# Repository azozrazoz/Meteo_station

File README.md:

# METEO BRASLET V1

My first device on PCB

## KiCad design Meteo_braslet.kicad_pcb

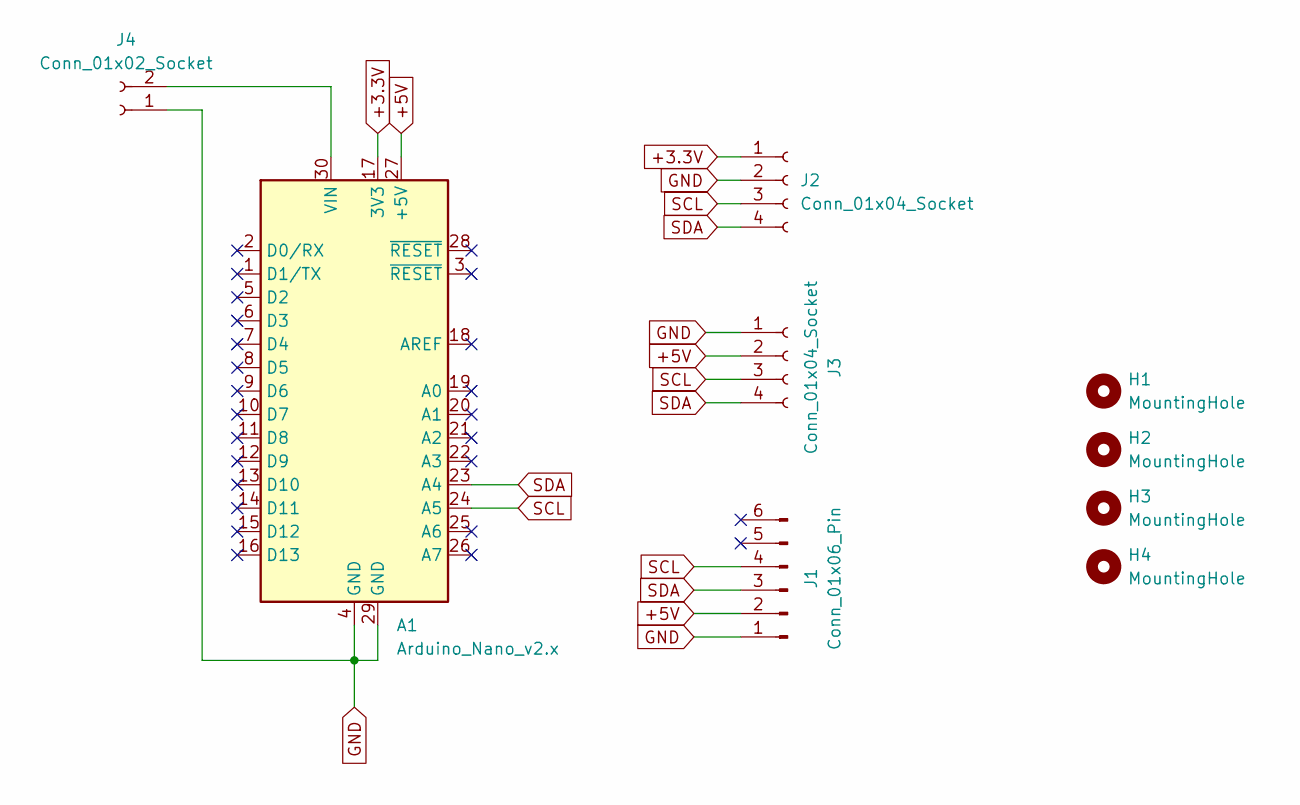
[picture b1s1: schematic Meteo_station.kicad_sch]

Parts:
A1: Arduino_Nano_v2.x; Arduino_Nano
H1, H2, H3, H4: MountingHole; MountingHole_2.5mm
J1: Conn_01x06_Pin; PinHeader_1x06_P2.54mm_Vertical
J2, J3: Conn_01x04_Socket; PinHeader_1x04_P2.54mm_Vertical
J4: Conn_01x02_Socket; PinHeader_1x02_P2.54mm_Vertical

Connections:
+3.3V: A1.17 (3V3), J2.1
+5V: A1.27 (+5V), J1.2, J3.2
GND: A1.4 (GND), A1.29 (GND), J1.1, J2.2, J3.1, J4.1
unnamed: A1.30 (VIN), J4.2
SCL: A1.24 (A5), J1.4, J2.3, J3.3
SDA: A1.23 (A4), J1.3, J2.4, J3.4

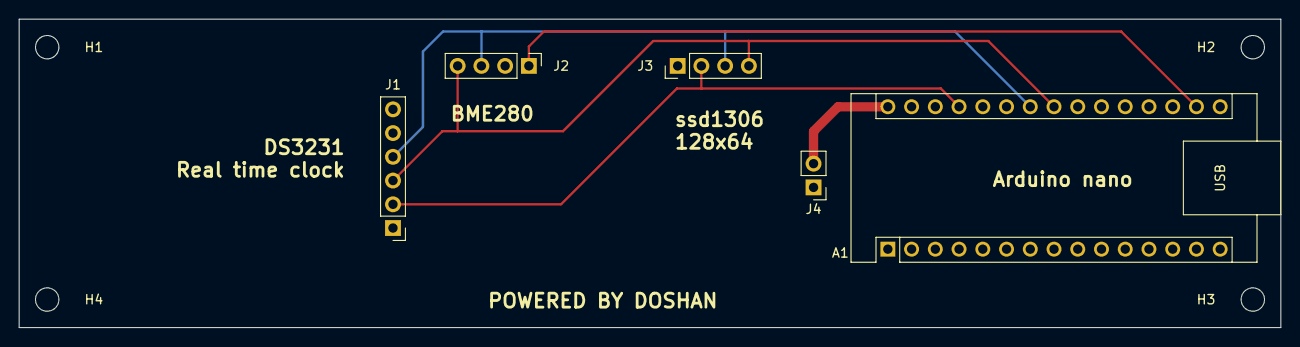
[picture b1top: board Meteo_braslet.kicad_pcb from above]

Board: 2 copper layers, 135.0 x 33.0 mm, 9 parts (0 on the bottom side), 6 nets.

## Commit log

2024-01-19 Rename Meteo_braslet.kicad_pcb to Meteo_staion.kicad_pcb
2024-01-19 Rename Meteo_braslet.kicad_prl to Meteo_staion.kicad_prl
2024-01-19 Rename Meteo_staion.kicad_prl to Meteo_station.kicad_prl
2024-01-19 Rename Meteo_staion.kicad_pcb to Meteo_station.kicad_pcb
2024-01-19 Rename Meteo_braslet.wrl to Meteo_station.wrl
2024-01-19 Rename Meteo_braslet.step to Meteo_station.step
2024-01-19 Rename Meteo_braslet.kicad_sch to Meteo_station.kicad_sch
2024-01-19 Rename Meteo_braslet.kicad_pro to Meteo_station.kicad_pro
2024-01-19 Rename Meteo_braslet-PTH.drl to Meteo_station-PTH.drl
2024-01-19 Rename Meteo_braslet-PTH-drl_map.gbr to Meteo_station-PTH-drl_map.gbr
2024-01-19 Rename Meteo_braslet-NPTH.drl to Meteo_station-NPTH.drl
2024-01-19 Rename Meteo_braslet-NPTH-drl_map.gbr to Meteo_station-NPTH-drl_map.gbr
2024-01-19 Rename Meteo_braslet-F_Silkscreen.gto to Meteo_station-F_Silkscreen.gto
2024-01-19 Rename Meteo_braslet-F_Paste.gtp to Meteo_station-F_Paste.gtp
2024-01-19 Rename Meteo_braslet-F_Mask.gts to Meteo_station-F_Mask.gts
2024-01-19 Rename Meteo_braslet-F_Cu.gtl to Meteo_station-F_Cu.gtl
2024-01-19 Rename Meteo_braslet-Edge_Cuts.gm1 to Meteo_station-Edge_Cuts.gm1
2024-01-19 Rename Meteo_braslet-B_Silkscreen.gbo to Meteo_station-B_Silkscreen.gbo
2024-01-19 Rename Meteo_braslet-B_Paste.gbp to Meteo_station-B_Paste.gbp
2024-01-19 Rename Meteo_braslet-B_Mask.gbs to Meteo_station-B_Mask.gbs
2024-01-19 Rename Meteo_braslet-B_Cu.gbl to Meteo_station-B_Cu.gbl
